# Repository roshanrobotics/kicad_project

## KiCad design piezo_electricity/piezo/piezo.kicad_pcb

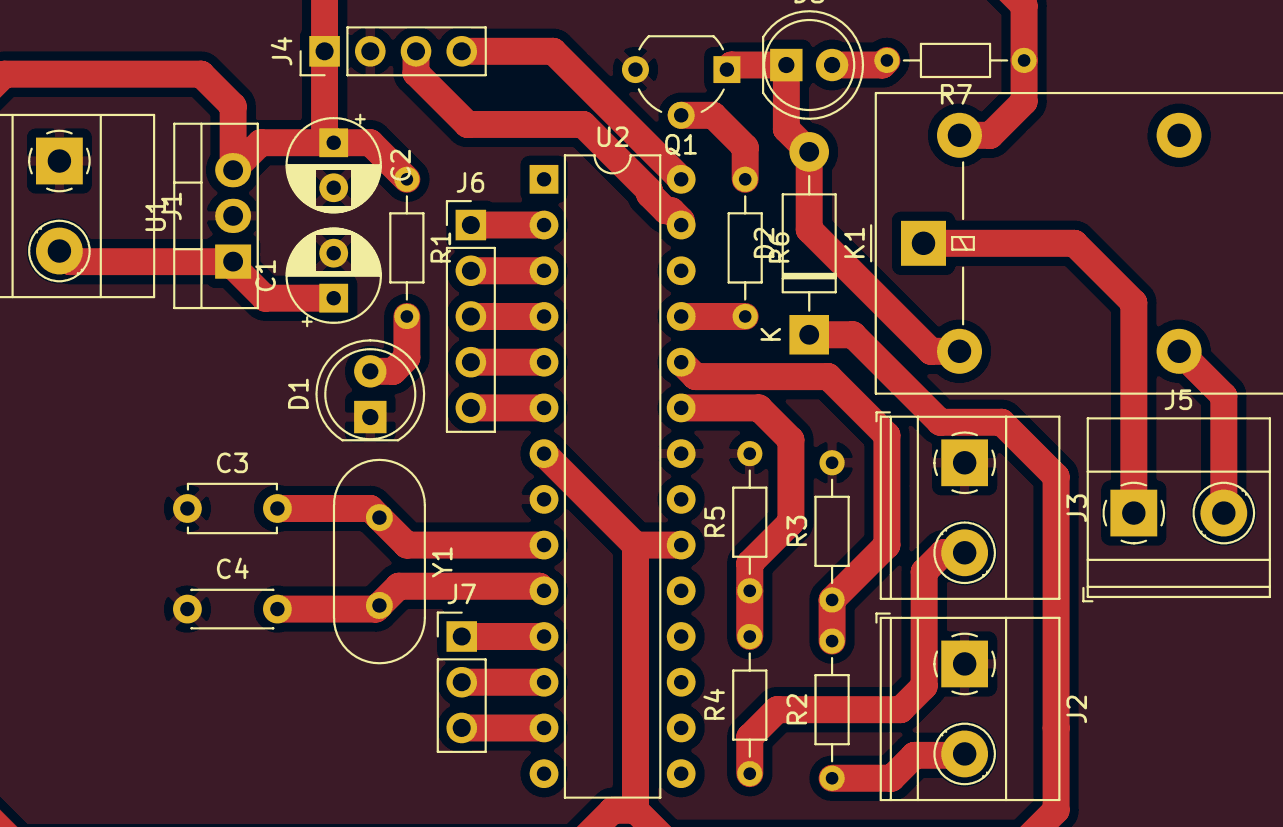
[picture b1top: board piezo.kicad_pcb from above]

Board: 2 copper layers, 26 parts (0 on the bottom side), 26 nets.

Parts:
C1: 10uf; CP_Radial_D5.0mm_P2.50mm
C2: 100uf; CP_Radial_D5.0mm_P2.50mm
C3: C_Small; C_Disc_D4.7mm_W2.5mm_P5.00mm
C4: C_Small; C_Disc_D4.3mm_W1.9mm_P5.00mm
D1, D3: LED; LED_D5.0mm
D2: 1N4007; D_DO-41_SOD81_P10.16mm_Horizontal
J1: Supply; TerminalBlock_Phoenix_MKDS-1,5-2_1x02_P5.00mm_Horizontal
J2: bat_conn; TerminalBlock_Phoenix_MKDS-1,5-2_1x02_P5.00mm_Horizontal
J3: piezo_conn; TerminalBlock_Phoenix_MKDS-1,5-2_1x02_P5.00mm_Horizontal
J4: LCd_conn; PinHeader_1x04_P2.54mm_Vertical
J5: Relay_conn; TerminalBlock_Phoenix_MKDS-1,5-2_1x02_P5.00mm_Horizontal
J6: Conn_05; PinHeader_1x05_P2.54mm_Vertical
J7: Conn_03; PinHeader_1x03_P2.54mm_Vertical
K1: G5LE-1; Relay_SPDT_Omron-G5LE-1
Q1: BC547; TO-92_Wide
R1, R2, R3, R4, R5: 330R; R_Axial_DIN0204_L3.6mm_D1.6mm_P7.62mm_Horizontal
R6, R7: R_Small; R_Axial_DIN0204_L3.6mm_D1.6mm_P7.62mm_Horizontal
U1: L7805; TO-220-3_Vertical
U2: ATmega328P-PU; DIP-28_W7.62mm
Y1: Crystal_Small; Crystal_HC49-U_Vertical

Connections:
+12V: C1.1, J1.2, U1.1
B_in: R2.2, R3.1, U2.24
GND: C1.2, C2.2, C3.1, C4.1, D1.1, J1.1, J2.1, J3.1, J4.2, Q1.3, R3.2, R5.2, U1.2, U2.8, U2.22
unnamed: C3.2, U2.9, Y1.1
unnamed: C4.2, U2.10, Y1.2
unnamed: D1.2, R1.2
unnamed: D2.2, D3.1, K1.2, Q1.1
unnamed: D3.2, R7.2
unnamed: J2.2, R2.1
unnamed: J3.2, R4.1
unnamed: J5.1, K1.1
unnamed: J5.2, K1.3
unnamed: J6.1, U2.2
unnamed: J6.2, U2.3
unnamed: J6.3, U2.4
unnamed: J6.4, U2.5
unnamed: J6.5, U2.6
unnamed: J7.1, U2.11
unnamed: J7.2, U2.12
unnamed: J7.3, U2.13
unnamed: Q1.2, R6.1
Pin: R4.2, R5.1, U2.23
Relay_pin: R6.2, U2.25
SCL: J4.4, U2.28
Sda: J4.3, U2.27
VCC: C2.1, D2.1, J4.1, K1.5, R1.1, R7.1, U1.3, U2.7, U2.20

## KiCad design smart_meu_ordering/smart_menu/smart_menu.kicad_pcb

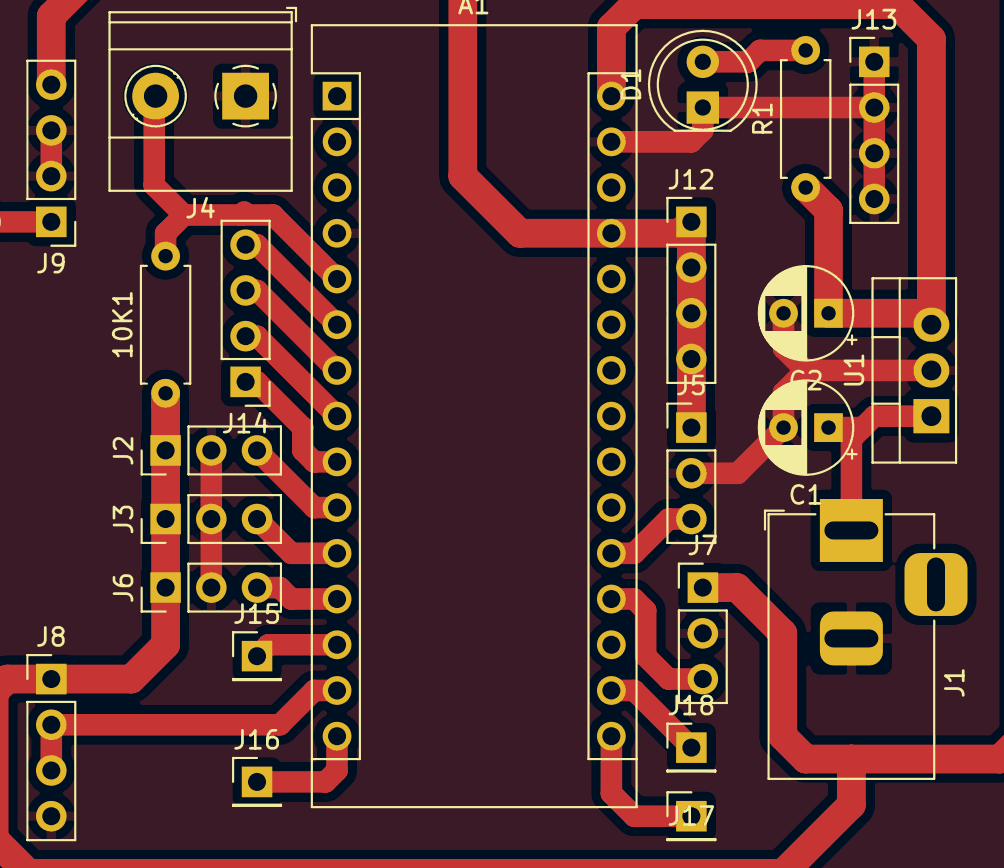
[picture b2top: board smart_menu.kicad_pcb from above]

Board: 2 copper layers, 23 parts (0 on the bottom side), 20 nets.

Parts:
10K1: R_Small; R_Axial_DIN0207_L6.3mm_D2.5mm_P7.62mm_Horizontal
A1: Arduino_Nano_v3.x; Arduino_Nano
C1, C2: C; CP_Radial_D5.0mm_P2.50mm
D1: LED; LED_D5.0mm
J1: Jack-DC; BarrelJack_Horizontal
J2: IR1_CONN; PinHeader_1x03_P2.54mm_Vertical
J3: IR2_CONN; PinHeader_1x03_P2.54mm_Vertical
J4: SWITCH; TerminalBlock_Phoenix_MKDS-1,5-2_1x02_P5.00mm_Horizontal
J5: IR5_CONN; PinHeader_1x03_P2.54mm_Vertical
J6: IR3_CONN; PinHeader_1x03_P2.54mm_Vertical
J7: IR4_CONN; PinHeader_1x03_P2.54mm_Vertical
J8: DATA_SIDE; PinHeader_1x04_P2.54mm_Vertical
J9: ANTENNA_SIDE; PinHeader_1x04_P2.54mm_Vertical
J12: VCc_Supply; PinHeader_1x04_P2.54mm_Vertical
J13: gnd_Supply; PinHeader_1x04_P2.54mm_Vertical
J14: MOTOR_CONN; PinHeader_1x04_P2.54mm_Vertical
J15: d10_conn; PinHeader_1x01_P2.54mm_Vertical
J16: d12_conn; PinHeader_1x01_P2.54mm_Vertical
J17: d13_conn; PinHeader_1x01_P2.54mm_Vertical
J18: 3v3; PinHeader_1x01_P2.54mm_Vertical
R1: R_Small; R_Axial_DIN0207_L6.3mm_D2.5mm_P7.62mm_Horizontal
U1: L7805; TO-220-3_Vertical

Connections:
+5V: A1.30, C2.1, R1.1, U1.3
GND: A1.4, A1.29, C1.2, C2.2, D1.1, J1.2, J2.2, J3.2, J4.1, J5.2, J6.2, J7.2, J8.4, J9.2, J9.3, J13.1, J13.2, J13.3, J13.4, U1.2
IR1_DATA: A1.10, J2.3
IR2_DATA: A1.11, J3.3
IR3_DATA: A1.12, J6.3
IR4_DATA: A1.19, J7.3
IR5_DATA: A1.20, J5.3
unnamed: A1.6, J14.4
unnamed: A1.7, J14.3
unnamed: A1.8, J14.2
unnamed: A1.9, J14.1
unnamed: A1.13, J15.1
unnamed: A1.15, J16.1
unnamed: A1.16, J17.1
unnamed: A1.17, J18.1
unnamed: C1.1, J1.1, U1.1
unnamed: D1.2, R1.2
RF_DATA: A1.14, J8.2, J8.3
SW: 10K1.2, A1.5, J4.2
VCC: 10K1.1, A1.27, J2.1, J3.1, J5.1, J6.1, J7.1, J8.1, J9.4, J12.1, J12.2, J12.3, J12.4
